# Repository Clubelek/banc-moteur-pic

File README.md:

# Banc de test moteur pour le PIC

Active load servo controlled (torque, speed, power).

## Specifications

* 1000-2500 RPM
* 0-3kW

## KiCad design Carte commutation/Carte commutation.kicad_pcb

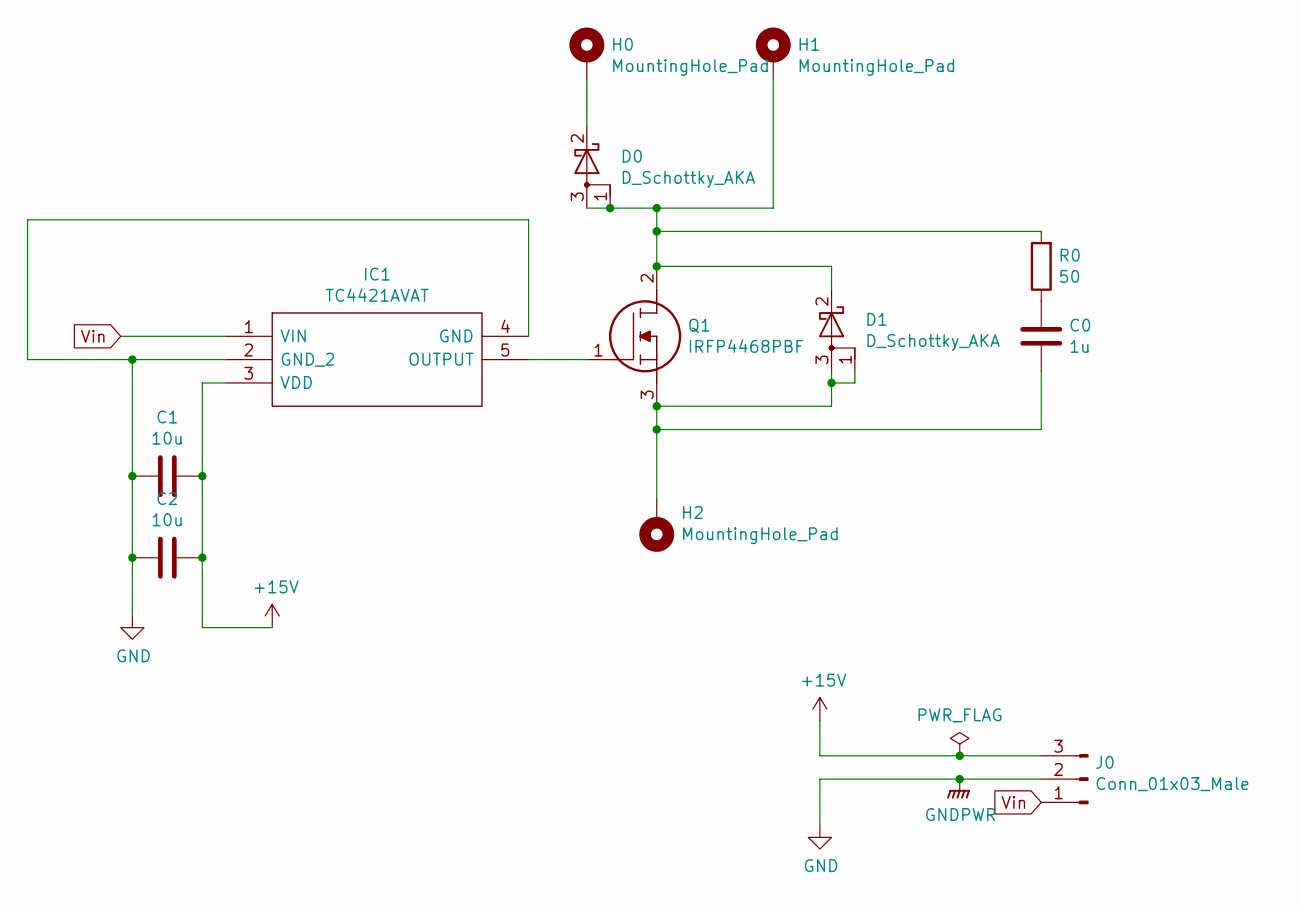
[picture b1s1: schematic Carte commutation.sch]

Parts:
C0: 1u; C_Rect_L7.2mm_W5.5mm_P5.00mm_FKS2_FKP2_MKS2_MKP2
C1, C2: 10u; C_0805_2012Metric_Pad1.15x1.40mm_HandSolder
D0, D1: D_Schottky_AKA; TO-220-3_Vertical
H0, H1, H2: MountingHole_Pad; MountingHole_8.4mm_M8_Pad_Via
IC1: TC4421AVAT; TO-220-5_P3.4x3.7mm_StaggerEven_Lead3.8mm_Vertical; Manufacturer_Part_Number TC4421AVAT; Mouser Part Number 579-TC4421AVAT
J0: Conn_01x03_Male; PinSocket_1x03_P2.54mm_Vertical
Q1: IRFP4468PBF; TO-247-3_Vertical; Manufacturer_Part_Number IRFP4468PBF
R0: 50; TO-263-2_TabPin1

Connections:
+15V: C1.1, C2.1, IC1.3 (VDD), J0.3
GND: C1.2, C2.2, IC1.2 (GND_2), IC1.4 (GND), J0.2
unnamed: C0.1, R0.1
unnamed: C0.2, D1.1 (A), D1.3 (A), H2.1, Q1.3
unnamed: D0.1 (A), D0.3 (A), D1.2 (K), H1.1, Q1.2, R0.2
unnamed: D0.2 (K), H0.1
unnamed: IC1.5 (OUTPUT), Q1.1
Vin: IC1.1 (VIN), J0.1

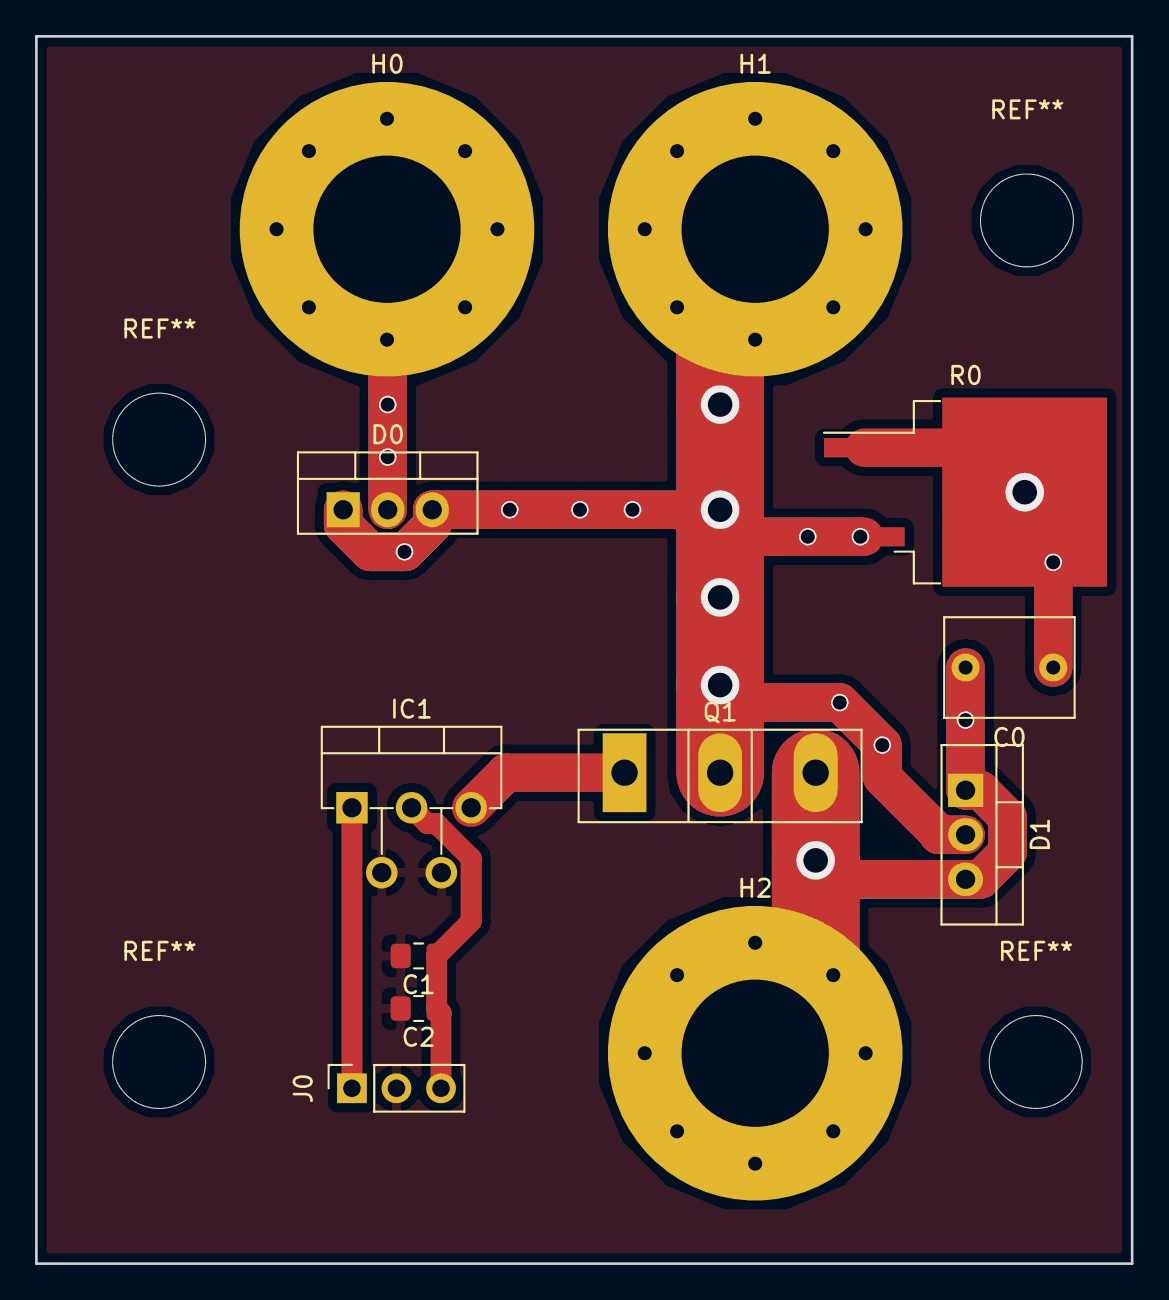
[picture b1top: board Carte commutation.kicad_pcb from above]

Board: 2 copper layers, 62.5 x 70.0 mm, 12 parts (0 on the bottom side), 8 nets.

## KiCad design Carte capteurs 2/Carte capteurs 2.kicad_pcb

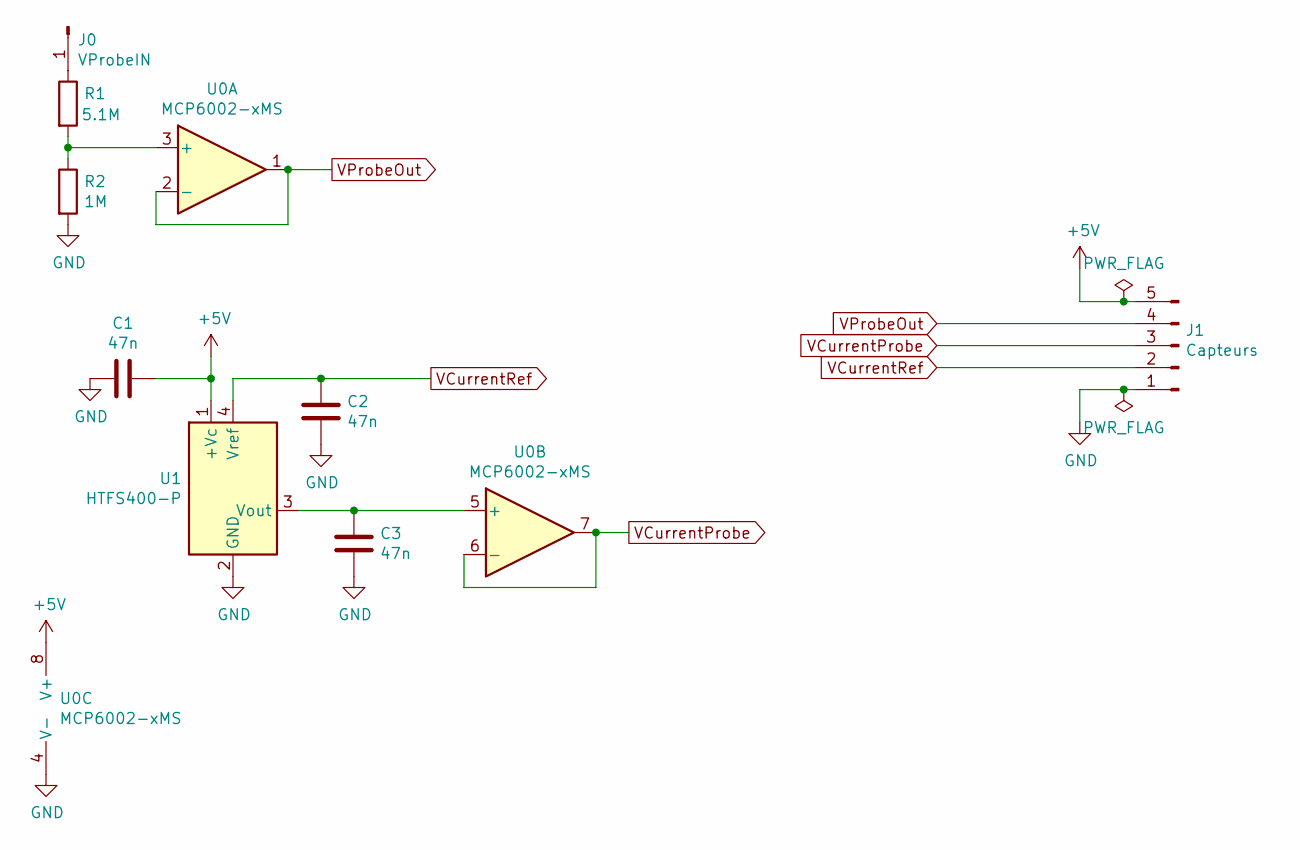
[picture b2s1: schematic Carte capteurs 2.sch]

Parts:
C1, C2, C3: 47n; C_0603_1608Metric
J0: VProbeIN; Pin_D1.3mm_L11.3mm_W2.8mm_Flat
J1: Capteurs; PinHeader_1x05_P2.54mm_Vertical
R1: 5.1M; R_0603_1608Metric
R2: 1M; R_0603_1608Metric
U0: MCP6002-xMS; SOIC-8_3.9x4.9mm_P1.27mm
U1: HTFS400-P; LEM_HTFS

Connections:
+5V: C1.1, J1.5, U0.8 (V+), U1.1 (+Vc)
GND: C1.2, C2.1, C3.2, J1.1, R2.2, U0.4 (V-), U1.2 (GND)
unnamed: C3.1, U0.5 (+), U1.3 (Vout)
unnamed: J0.1, R1.1
unnamed: R1.2, R2.1, U0.3 (+)
VCurrentProbe: J1.3, U0.6 (-), U0.7
VCurrentRef: C2.2, J1.2, U1.4 (Vref)
VProbeOut: J1.4, U0.1, U0.2 (-)

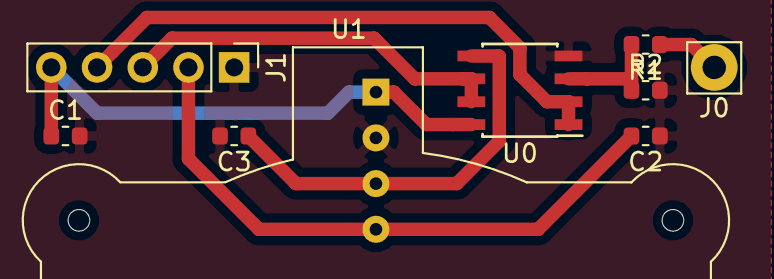
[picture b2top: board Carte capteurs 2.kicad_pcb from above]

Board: 2 copper layers, 9 parts (0 on the bottom side), 8 nets.

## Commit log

2020-06-07 Writting Report
